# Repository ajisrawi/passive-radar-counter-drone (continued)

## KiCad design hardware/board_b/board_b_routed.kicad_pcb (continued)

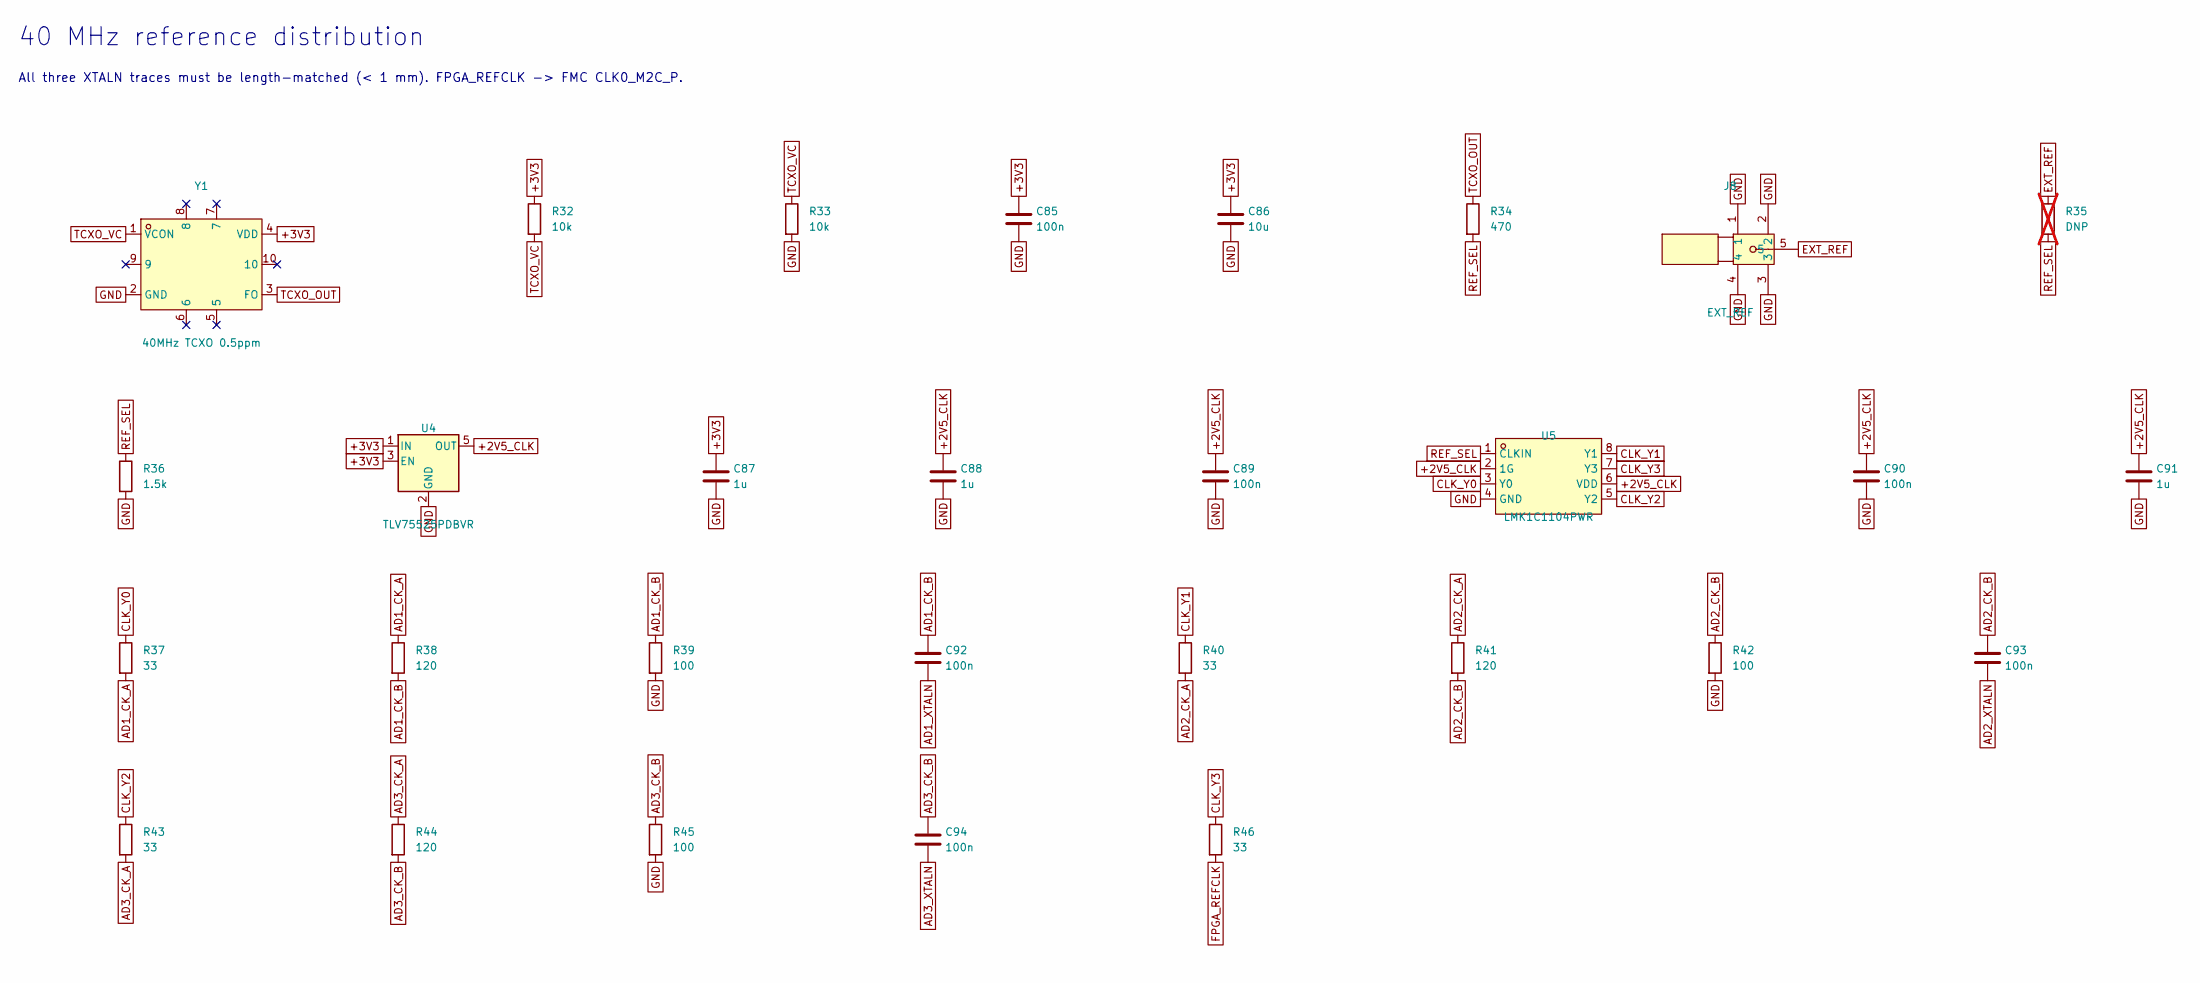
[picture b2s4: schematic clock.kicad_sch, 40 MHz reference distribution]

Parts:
C85, C89, C90, C92, C93, C94: 100n; C_0402_1005Metric; LCSC C1525
C86: 10u; C_0603_1608Metric; LCSC C19702
C87, C88, C91: 1u; C_0402_1005Metric; LCSC C52923
J8: EXT_REF; SMA-TH_BWSMA-KE-Z001; MPN BWSMA-KE-Z001; LCSC C496549
R32, R33: 10k; R_0402_1005Metric; LCSC C25744
R34: 470; R_0402_1005Metric
R35: DNP; R_0402_1005Metric; not fitted
R36: 1.5k; R_0402_1005Metric
R37, R40, R43, R46: 33; R_0402_1005Metric
R38, R41, R44: 120; R_0402_1005Metric
R39, R42, R45: 100; R_0402_1005Metric
U4: TLV75525PDBVR; SOT-23-5
U5: LMK1C1104PWR; TSSOP-8_L4.4-W3.0-P0.65-LS6.4-TL; MPN LMK1C1104PWR; LCSC C1855734
Y1: 40MHz TCXO 0.5ppm; OSC-SMD_10P-L7.0-W5.0-BL; MPN BT0507BH3I507BN40B; LCSC C516506

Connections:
+2V5_CLK: C88.1, C89.1, C90.1, C91.1, U4.5 (OUT), U5.2 (1G), U5.6 (VDD)
+3V3: C85.1, C86.1, C87.1, R32.1, U4.1 (IN), U4.3 (EN), Y1.4 (VDD); also elsewhere on the board
AD1_CK_A: R37.2, R38.1
AD1_CK_B: C92.1, R38.2, R39.1
AD1_XTALN: C92.2; also elsewhere on the board
AD2_CK_A: R40.2, R41.1
AD2_CK_B: C93.1, R41.2, R42.1
AD2_XTALN: C93.2; also elsewhere on the board
AD3_CK_A: R43.2, R44.1
AD3_CK_B: C94.1, R44.2, R45.1
AD3_XTALN: C94.2; also elsewhere on the board
CLK_Y0: R37.1, U5.3 (Y0)
CLK_Y1: R40.1, U5.8 (Y1)
CLK_Y2: R43.1, U5.5 (Y2)
CLK_Y3: R46.1, U5.7 (Y3)
EXT_REF: J8.5, R35.1
FPGA_REFCLK: R46.2; also elsewhere on the board
GND: C85.2, C86.2, C87.2, C88.2, C89.2, C90.2, C91.2, J8.1, J8.2, J8.3, J8.4, R33.2, R36.2, R39.2, R42.2, R45.2, U4.2 (GND), U5.4 (GND), Y1.2 (GND); also elsewhere on the board
REF_SEL: R34.2, R35.2, R36.1, U5.1 (CLKIN)
TCXO_OUT: R34.1, Y1.3 (FO)
TCXO_VC: R32.2, R33.1, Y1.1 (VCON)

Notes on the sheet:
40 MHz reference distribution
All three XTALN traces must be length-matched (< 1 mm). FPGA_REFCLK -> FMC CLK0_M2C_P.

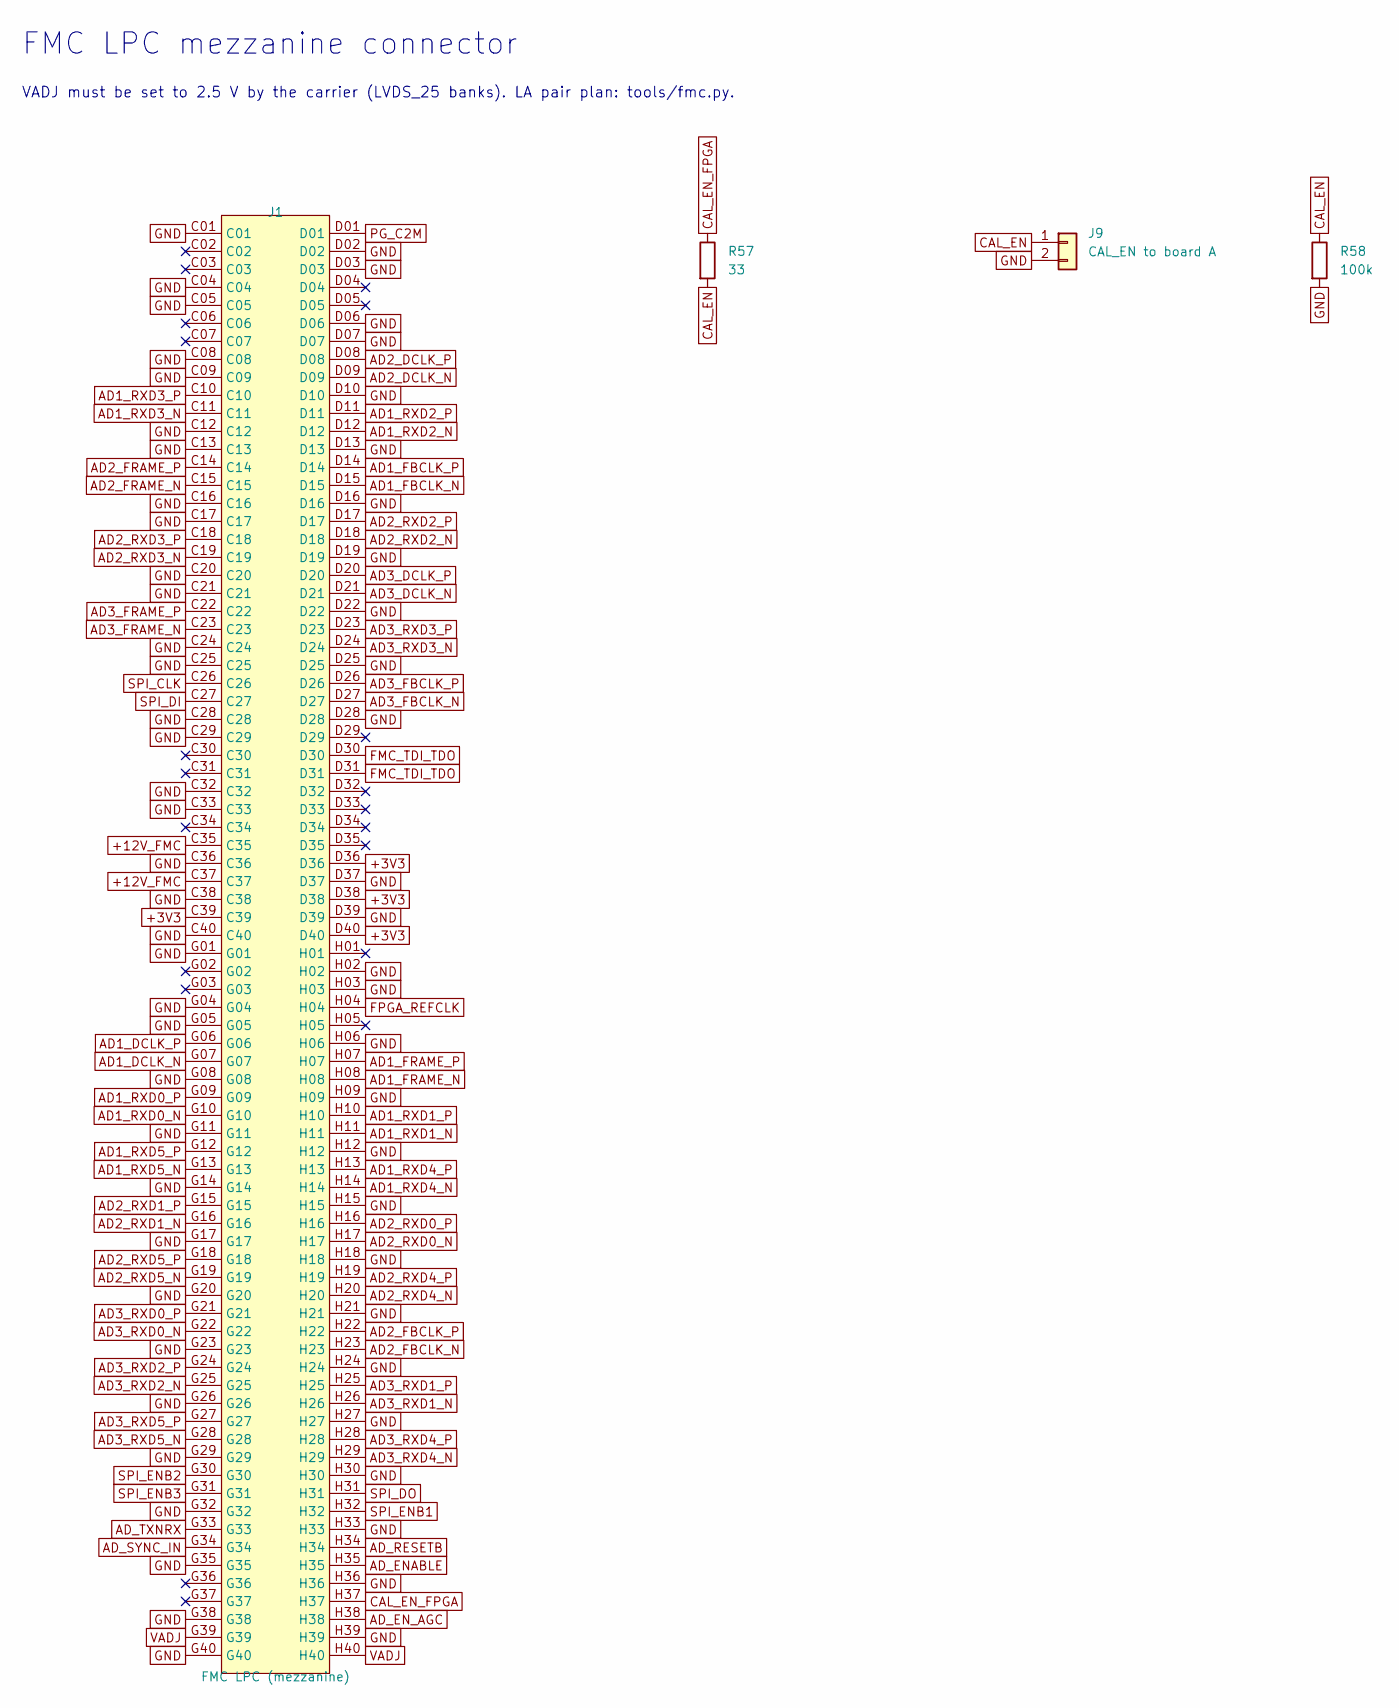
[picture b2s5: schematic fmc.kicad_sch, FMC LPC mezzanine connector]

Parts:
J1: FMC LPC (mezzanine); FPC_SMD_ASP-134604-01; MPN ASP-134604-01; LCSC C2830435
J9: CAL_EN to board A; PinHeader_1x02_P2.54mm_Vertical
R57: 33; R_0402_1005Metric
R58: 100k; R_0402_1005Metric; LCSC C25741

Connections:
+3V3: J1.C39, J1.D36, J1.D38, J1.D40; also elsewhere on the board
+12V_FMC: J1.C35, J1.C37; also elsewhere on the board
AD1_DCLK_N: J1.G07; also elsewhere on the board
AD1_DCLK_P: J1.G06; also elsewhere on the board
AD1_FBCLK_N: J1.D15; also elsewhere on the board
AD1_FBCLK_P: J1.D14; also elsewhere on the board
AD1_FRAME_N: J1.H08; also elsewhere on the board
AD1_FRAME_P: J1.H07; also elsewhere on the board
AD1_RXD0_N: J1.G10; also elsewhere on the board
AD1_RXD0_P: J1.G09; also elsewhere on the board
AD1_RXD1_N: J1.H11; also elsewhere on the board
AD1_RXD1_P: J1.H10; also elsewhere on the board
AD1_RXD2_N: J1.D12; also elsewhere on the board
AD1_RXD2_P: J1.D11; also elsewhere on the board
AD1_RXD3_N: J1.C11; also elsewhere on the board
AD1_RXD3_P: J1.C10; also elsewhere on the board
AD1_RXD4_N: J1.H14; also elsewhere on the board
AD1_RXD4_P: J1.H13; also elsewhere on the board
AD1_RXD5_N: J1.G13; also elsewhere on the board
AD1_RXD5_P: J1.G12; also elsewhere on the board
AD2_DCLK_N: J1.D09; also elsewhere on the board
AD2_DCLK_P: J1.D08; also elsewhere on the board
AD2_FBCLK_N: J1.H23; also elsewhere on the board
AD2_FBCLK_P: J1.H22; also elsewhere on the board
AD2_FRAME_N: J1.C15; also elsewhere on the board
AD2_FRAME_P: J1.C14; also elsewhere on the board
AD2_RXD0_N: J1.H17; also elsewhere on the board
AD2_RXD0_P: J1.H16; also elsewhere on the board
AD2_RXD1_N: J1.G16; also elsewhere on the board
AD2_RXD1_P: J1.G15; also elsewhere on the board
AD2_RXD2_N: J1.D18; also elsewhere on the board
AD2_RXD2_P: J1.D17; also elsewhere on the board
AD2_RXD3_N: J1.C19; also elsewhere on the board
AD2_RXD3_P: J1.C18; also elsewhere on the board
AD2_RXD4_N: J1.H20; also elsewhere on the board
AD2_RXD4_P: J1.H19; also elsewhere on the board
AD2_RXD5_N: J1.G19; also elsewhere on the board
AD2_RXD5_P: J1.G18; also elsewhere on the board
AD3_DCLK_N: J1.D21; also elsewhere on the board
AD3_DCLK_P: J1.D20; also elsewhere on the board
AD3_FBCLK_N: J1.D27; also elsewhere on the board
AD3_FBCLK_P: J1.D26; also elsewhere on the board
AD3_FRAME_N: J1.C23; also elsewhere on the board
AD3_FRAME_P: J1.C22; also elsewhere on the board
AD3_RXD0_N: J1.G22; also elsewhere on the board
AD3_RXD0_P: J1.G21; also elsewhere on the board
AD3_RXD1_N: J1.H26; also elsewhere on the board
AD3_RXD1_P: J1.H25; also elsewhere on the board
AD3_RXD2_N: J1.G25; also elsewhere on the board
AD3_RXD2_P: J1.G24; also elsewhere on the board
AD3_RXD3_N: J1.D24; also elsewhere on the board
AD3_RXD3_P: J1.D23; also elsewhere on the board
AD3_RXD4_N: J1.H29; also elsewhere on the board
AD3_RXD4_P: J1.H28; also elsewhere on the board
AD3_RXD5_N: J1.G28; also elsewhere on the board
AD3_RXD5_P: J1.G27; also elsewhere on the board
AD_ENABLE: J1.H35; also elsewhere on the board
AD_EN_AGC: J1.H38; also elsewhere on the board
AD_RESETB: J1.H34; also elsewhere on the board
AD_SYNC_IN: J1.G34; also elsewhere on the board
AD_TXNRX: J1.G33; also elsewhere on the board
CAL_EN: J9.1, R57.2, R58.1
CAL_EN_FPGA: J1.H37, R57.1
FMC_TDI_TDO: J1.D30, J1.D31
FPGA_REFCLK: J1.H04; also elsewhere on the board
GND: J1.C01, J1.C04, J1.C05, J1.C08, J1.C09, J1.C12, J1.C13, J1.C16, J1.C17, J1.C20, J1.C21, J1.C24, J1.C25, J1.C28, J1.C29, J1.C32, J1.C33, J1.C36, J1.C38, J1.C40, J1.D02, J1.D03, J1.D06, J1.D07, J1.D10, J1.D13, J1.D16, J1.D19, J1.D22, J1.D25, J1.D28, J1.D37, J1.D39, J1.G01, J1.G04, J1.G05, J1.G08, J1.G11, J1.G14, J1.G17, J1.G20, J1.G23, J1.G26, J1.G29, J1.G32, J1.G35, J1.G38, J1.G40, J1.H02, J1.H03, J1.H06, J1.H09, J1.H12, J1.H15, J1.H18, J1.H21, J1.H24, J1.H27, J1.H30, J1.H33, J1.H36, J1.H39, J9.2, R58.2; also elsewhere on the board
PG_C2M: J1.D01; also elsewhere on the board
SPI_CLK: J1.C26; also elsewhere on the board
SPI_DI: J1.C27; also elsewhere on the board
SPI_DO: J1.H31; also elsewhere on the board
SPI_ENB1: J1.H32; also elsewhere on the board
SPI_ENB2: J1.G30; also elsewhere on the board
SPI_ENB3: J1.G31; also elsewhere on the board
VADJ: J1.G39, J1.H40; also elsewhere on the board

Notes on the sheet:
FMC LPC mezzanine connector
VADJ must be set to 2.5 V by the carrier (LVDS_25 banks). LA pair plan: tools/fmc.py.

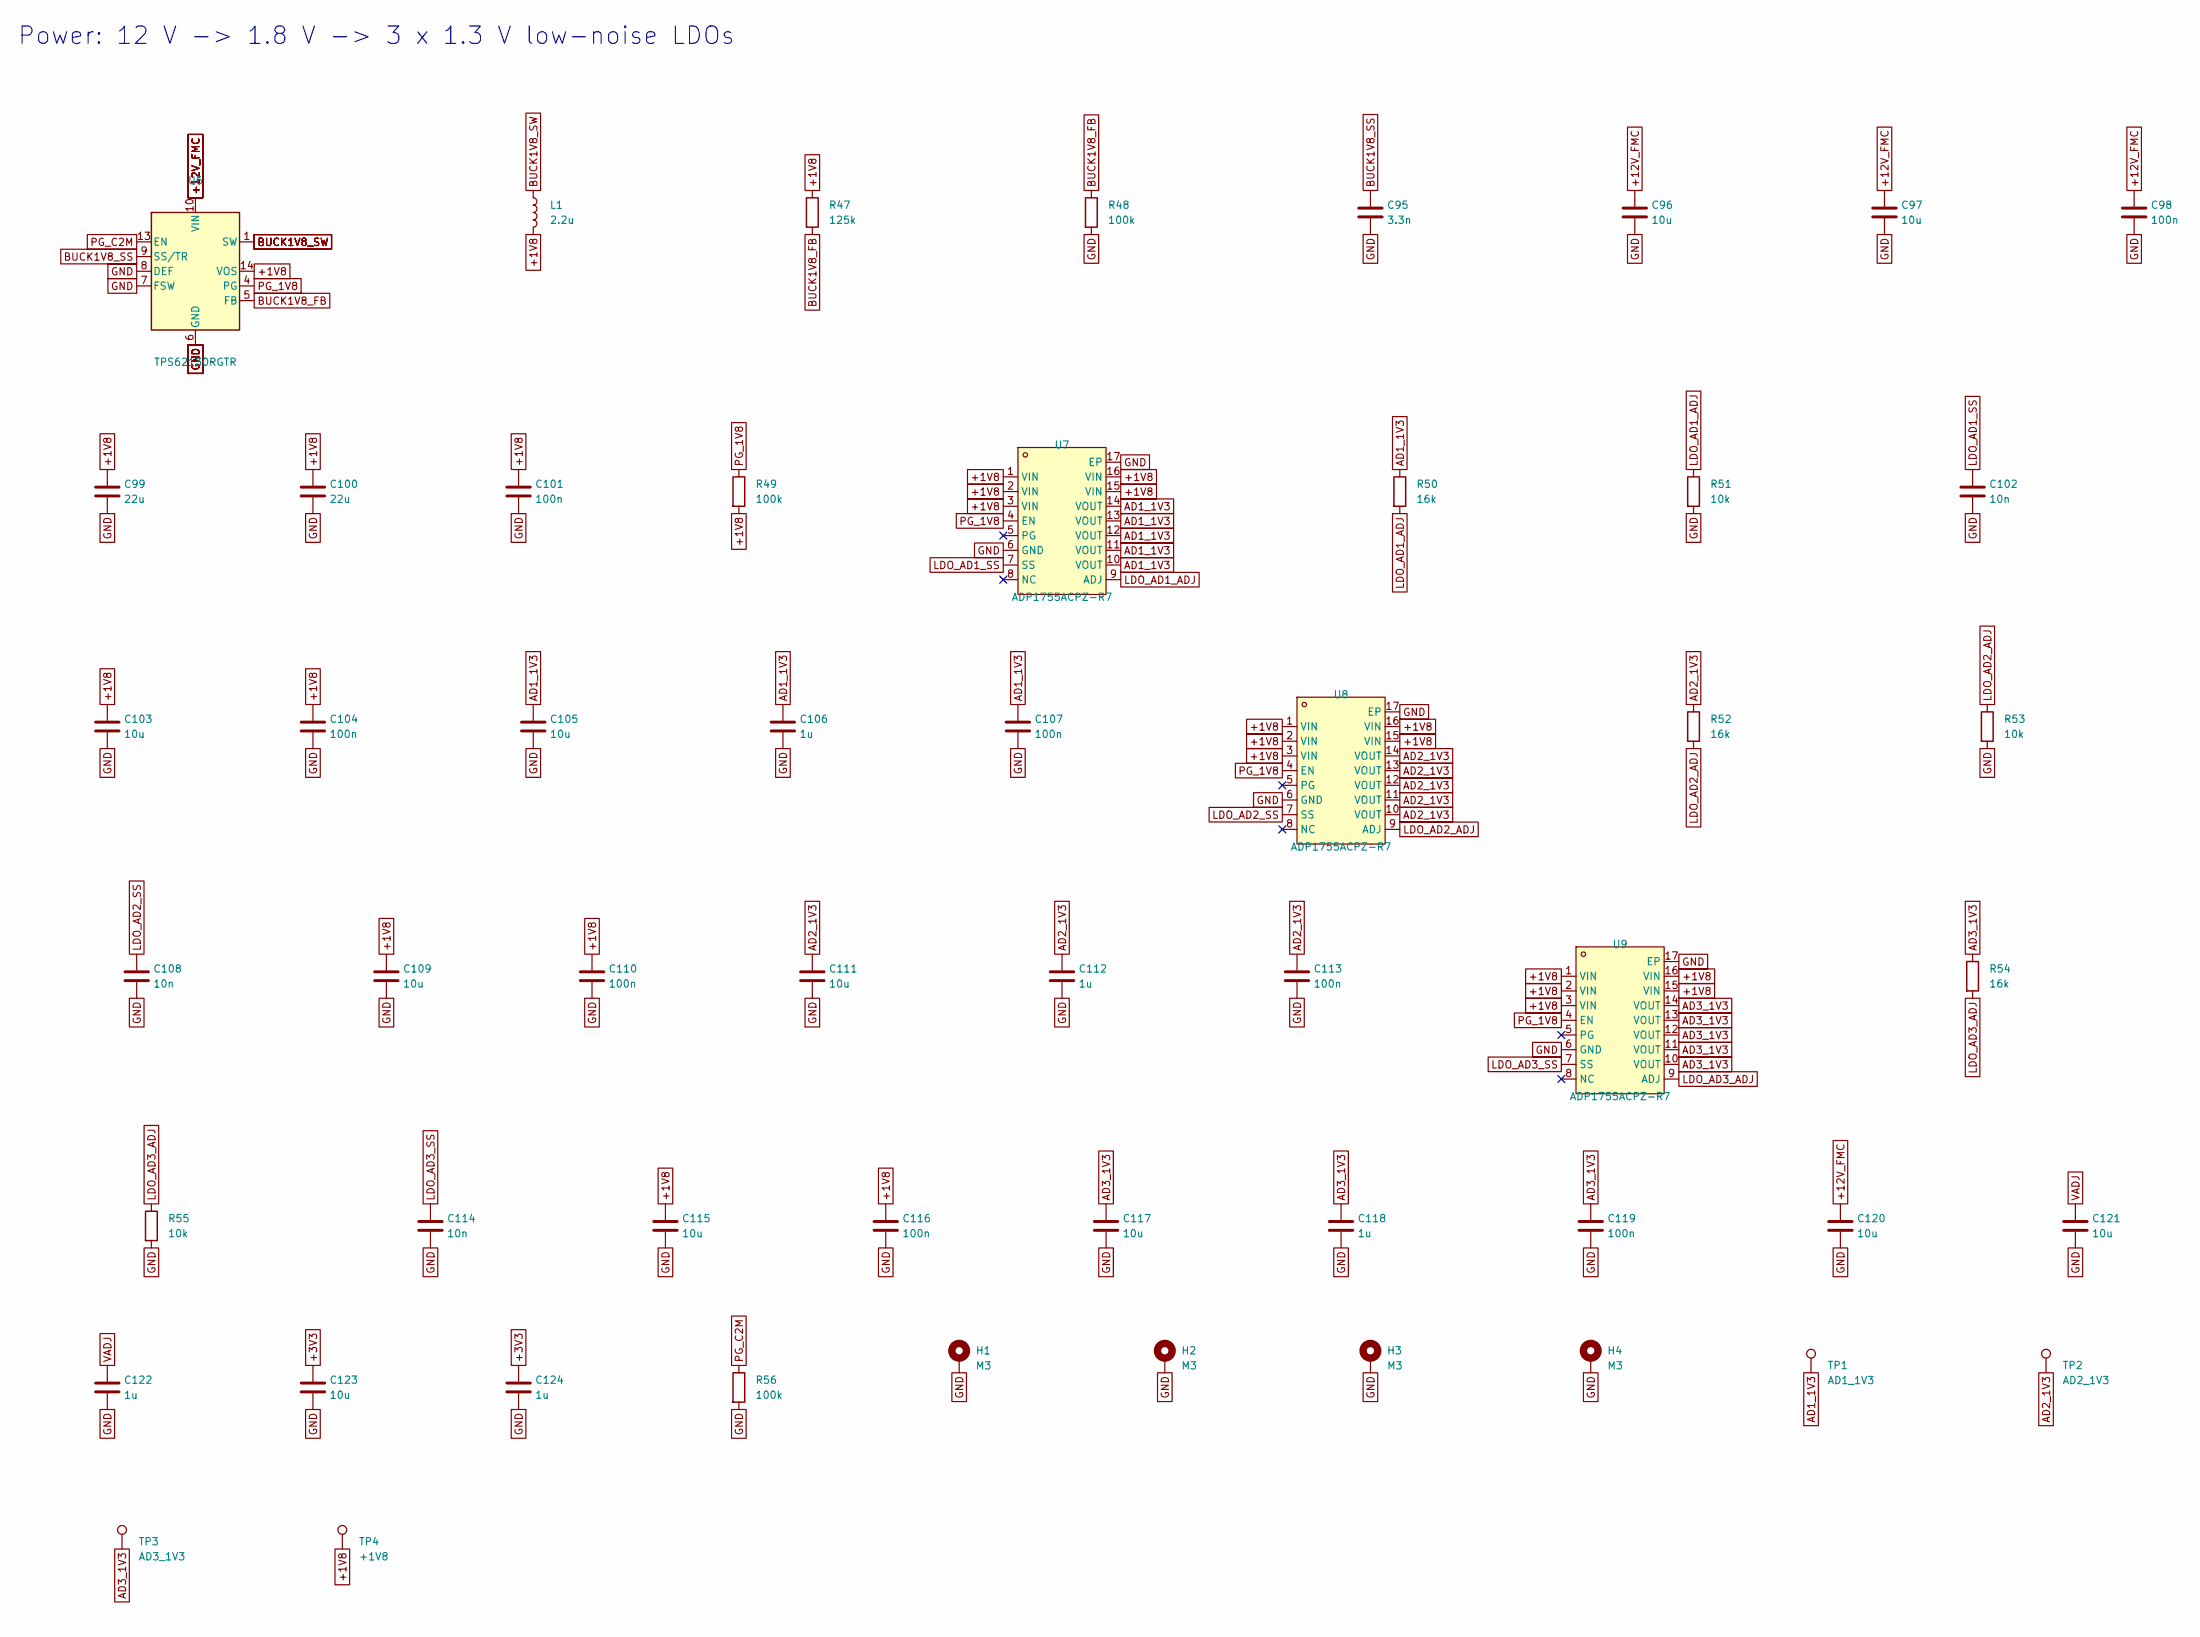
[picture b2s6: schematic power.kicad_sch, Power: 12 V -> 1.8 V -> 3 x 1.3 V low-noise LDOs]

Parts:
C95: 3.3n; C_0402_1005Metric
C96, C97, C120: 10u; C_0805_2012Metric
C98, C101, C104, C107, C110, C113, C116, C119: 100n; C_0402_1005Metric; LCSC C1525
C99, C100: 22u; C_0805_2012Metric; LCSC C45783
C102, C108, C114: 10n; C_0402_1005Metric; LCSC C15195
C103, C105, C109, C111, C115, C117, C121, C123: 10u; C_0603_1608Metric; LCSC C19702
C106, C112, C118, C122, C124: 1u; C_0402_1005Metric; LCSC C52923
H1, H2, H3, H4: M3; MountingHole_3.2mm_M3_Pad_Via
L1: 2.2u; L_Bourns-SRN4018; MPN SRN4018-2R2M
R47: 125k; R_0402_1005Metric
R48, R49, R56: 100k; R_0402_1005Metric; LCSC C25741
R50, R52, R54: 16k; R_0402_1005Metric; Tolerance 1%
R51, R53, R55: 10k; R_0402_1005Metric; Tolerance 1%; LCSC C25744
TP1: AD1_1V3; TestPoint_Pad_D1.0mm
TP2: AD2_1V3; TestPoint_Pad_D1.0mm
TP3: AD3_1V3; TestPoint_Pad_D1.0mm
TP4: +1V8; TestPoint_Pad_D1.0mm
U6: TPS62130RGTR; VQFN-16-1EP_3x3mm_P0.5mm_EP1.68x1.68mm; MPN TPS62130RGTR; LCSC C43590
U7, U8, U9: ADP1755ACPZ-R7; LFCSP-16_L4.0-W4.0-P0.65-BL-EP2.2; MPN ADP1755ACPZ-R7; LCSC C403695

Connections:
+1V8: C99.1, C100.1, C101.1, C103.1, C104.1, C109.1, C110.1, C115.1, C116.1, L1.2, R47.1, R49.2, TP4.1, U6.14 (VOS), U7.1 (VIN), U7.2 (VIN), U7.3 (VIN), U7.15 (VIN), U7.16 (VIN), U8.1 (VIN), U8.2 (VIN), U8.3 (VIN), U8.15 (VIN), U8.16 (VIN), U9.1 (VIN), U9.2 (VIN), U9.3 (VIN), U9.15 (VIN), U9.16 (VIN)
+3V3: C123.1, C124.1; also elsewhere on the board
+12V_FMC: C96.1, C97.1, C98.1, C120.1, U6.10 (VIN), U6.11 (VIN), U6.12 (VIN); also elsewhere on the board
AD1_1V3: C105.1, C106.1, C107.1, R50.1, TP1.1, U7.10 (VOUT), U7.11 (VOUT), U7.12 (VOUT), U7.13 (VOUT), U7.14 (VOUT); also elsewhere on the board
AD2_1V3: C111.1, C112.1, C113.1, R52.1, TP2.1, U8.10 (VOUT), U8.11 (VOUT), U8.12 (VOUT), U8.13 (VOUT), U8.14 (VOUT); also elsewhere on the board
AD3_1V3: C117.1, C118.1, C119.1, R54.1, TP3.1, U9.10 (VOUT), U9.11 (VOUT), U9.12 (VOUT), U9.13 (VOUT), U9.14 (VOUT); also elsewhere on the board
BUCK1V8_FB: R47.2, R48.1, U6.5 (FB)
BUCK1V8_SS: C95.1, U6.9 (SS/TR)
BUCK1V8_SW: L1.1, U6.1 (SW), U6.2 (SW), U6.3 (SW)
GND: C95.2, C96.2, C97.2, C98.2, C99.2, C100.2, C101.2, C102.2, C103.2, C104.2, C105.2, C106.2, C107.2, C108.2, C109.2, C110.2, C111.2, C112.2, C113.2, C114.2, C115.2, C116.2, C117.2, C118.2, C119.2, C120.2, C121.2, C122.2, C123.2, C124.2, H1.1, H2.1, H3.1, H4.1, R48.2, R51.2, R53.2, R55.2, R56.2, U6.6 (GND), U6.7 (FSW), U6.8 (DEF), U6.15 (GND), U6.16 (GND), U6.17 (GND), U7.6 (GND), U7.17 (EP), U8.6 (GND), U8.17 (EP), U9.6 (GND), U9.17 (EP); also elsewhere on the board
LDO_AD1_ADJ: R50.2, R51.1, U7.9 (ADJ)
LDO_AD1_SS: C102.1, U7.7 (SS)
LDO_AD2_ADJ: R52.2, R53.1, U8.9 (ADJ)
LDO_AD2_SS: C108.1, U8.7 (SS)
LDO_AD3_ADJ: R54.2, R55.1, U9.9 (ADJ)
LDO_AD3_SS: C114.1, U9.7 (SS)
PG_1V8: R49.1, U6.4 (PG), U7.4 (EN), U8.4 (EN), U9.4 (EN)
PG_C2M: R56.1, U6.13 (EN); also elsewhere on the board
VADJ: C121.1, C122.1; also elsewhere on the board

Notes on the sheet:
Power: 12 V -> 1.8 V -> 3 x 1.3 V low-noise LDOs

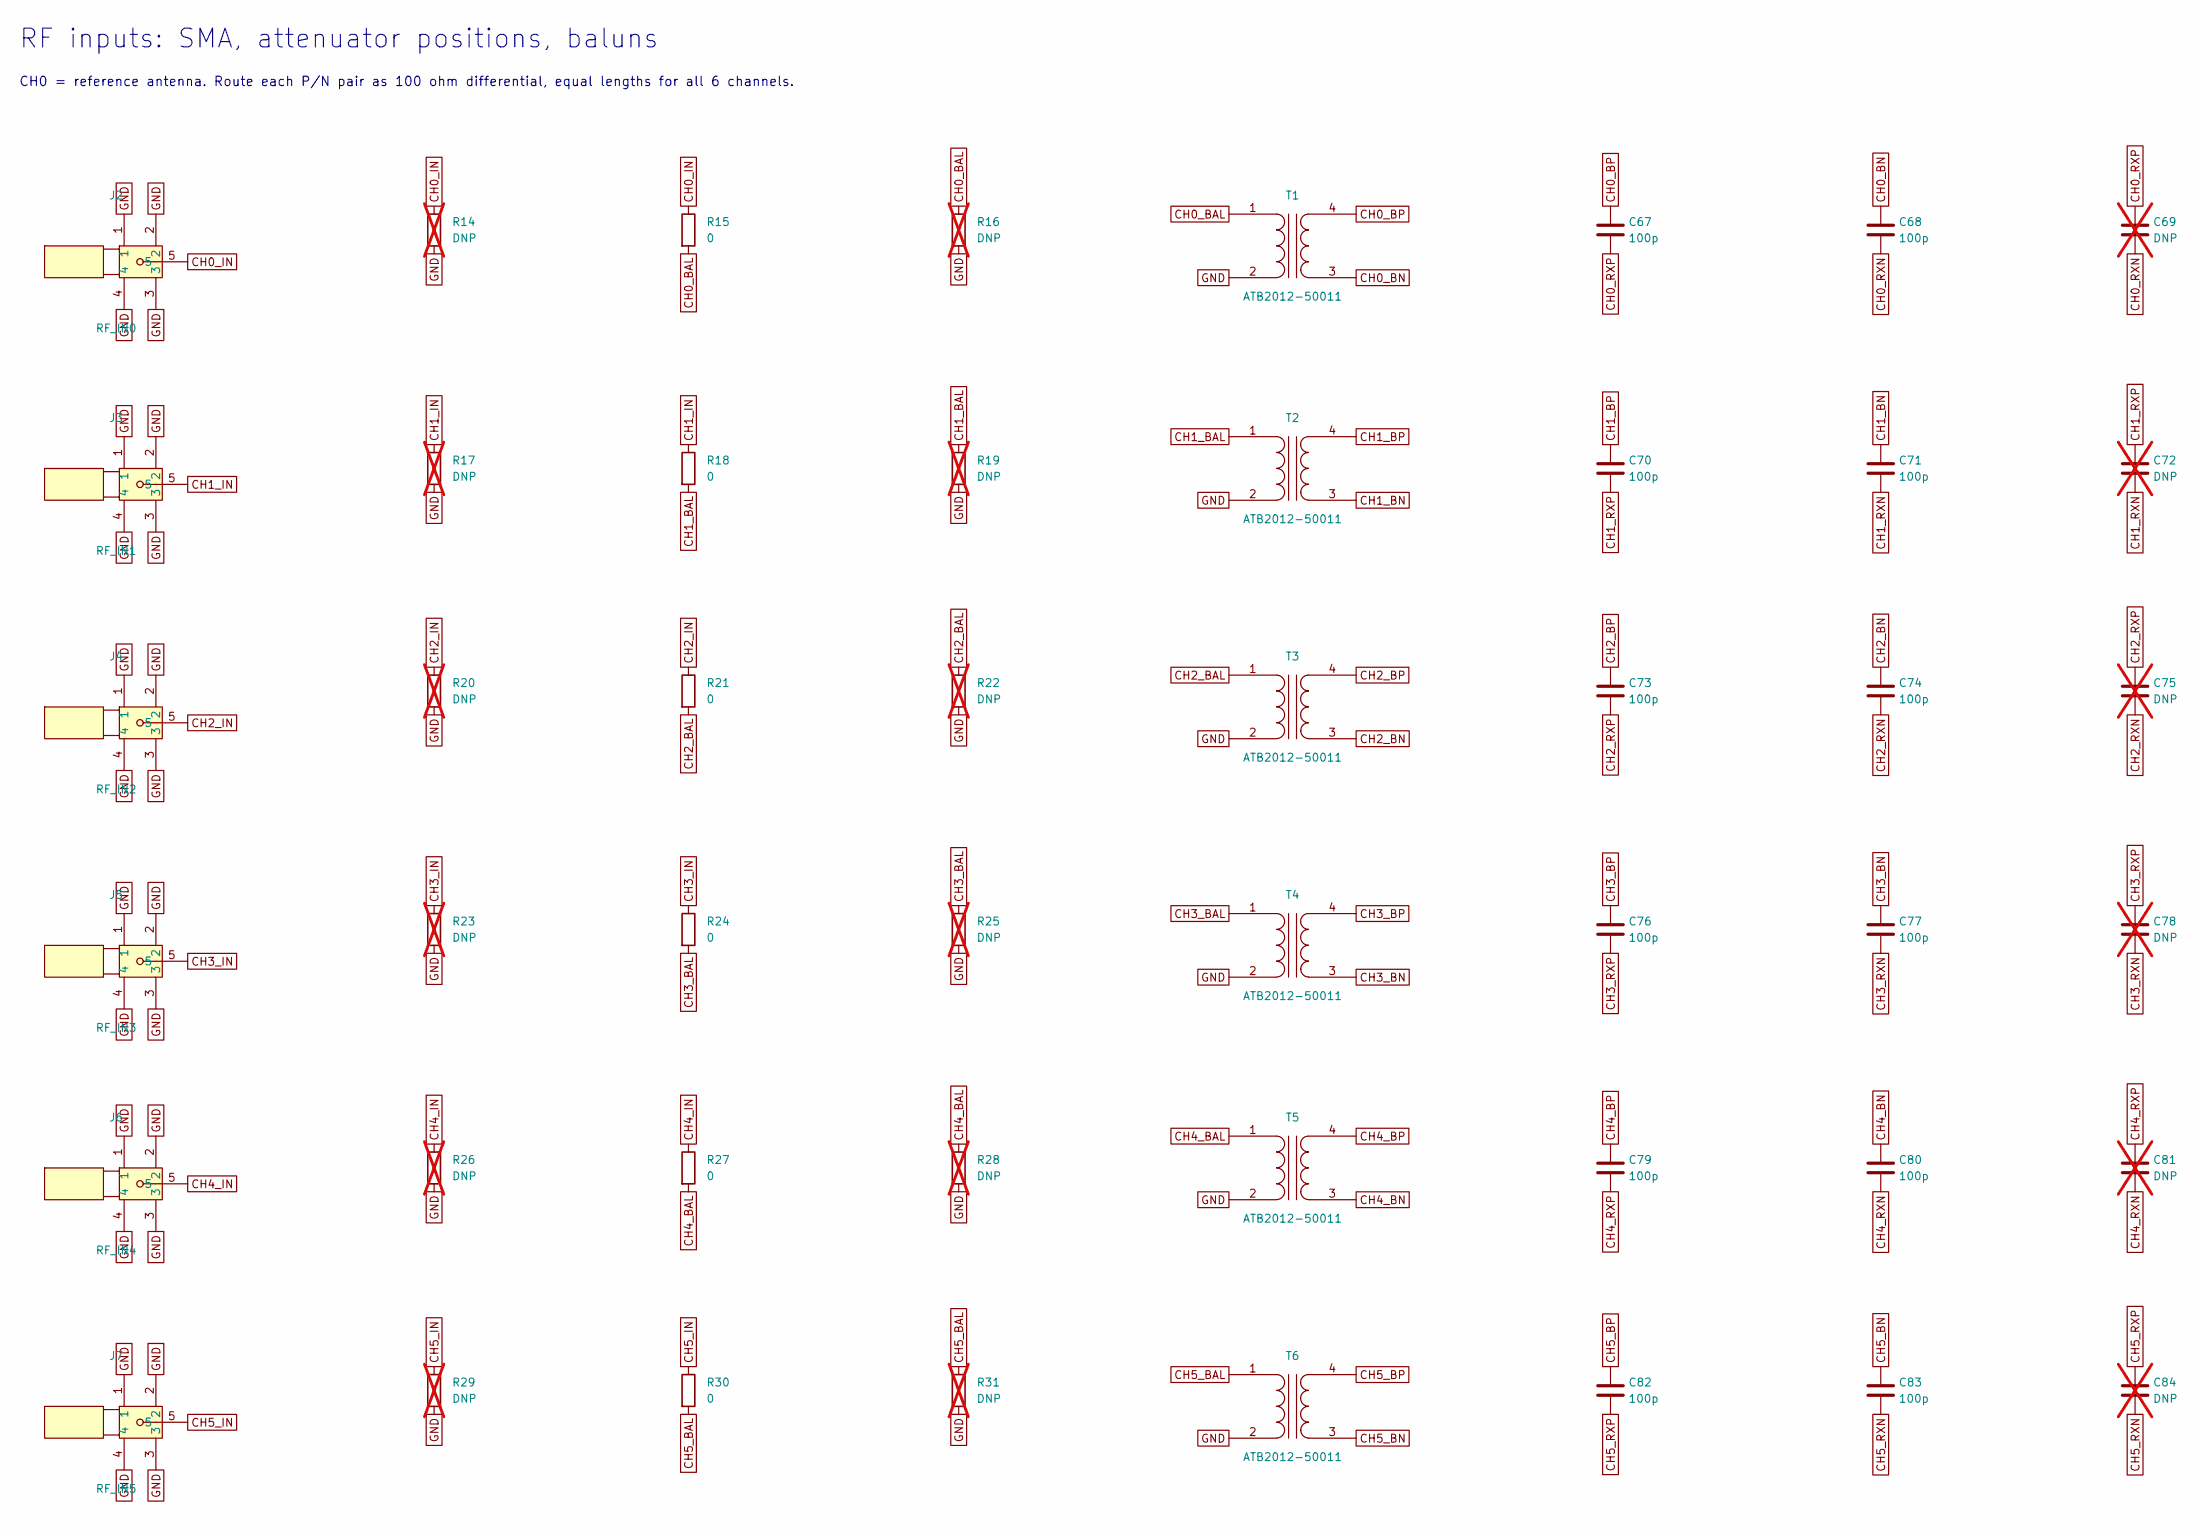
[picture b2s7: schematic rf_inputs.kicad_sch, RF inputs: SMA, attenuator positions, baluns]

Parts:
C67, C68, C70, C71, C73, C74, C76, C77, C79, C80, C82, C83: 100p; C_0402_1005Metric
C69, C72, C75, C78, C81, C84: DNP; C_0402_1005Metric; not fitted
J2: RF_IN0; SMA-TH_BWSMA-KE-Z001; MPN BWSMA-KE-Z001; LCSC C496549
J3: RF_IN1; SMA-TH_BWSMA-KE-Z001; MPN BWSMA-KE-Z001; LCSC C496549
J4: RF_IN2; SMA-TH_BWSMA-KE-Z001; MPN BWSMA-KE-Z001; LCSC C496549
J5: RF_IN3; SMA-TH_BWSMA-KE-Z001; MPN BWSMA-KE-Z001; LCSC C496549
J6: RF_IN4; SMA-TH_BWSMA-KE-Z001; MPN BWSMA-KE-Z001; LCSC C496549
J7: RF_IN5; SMA-TH_BWSMA-KE-Z001; MPN BWSMA-KE-Z001; LCSC C496549
R14, R16, R17, R19, R20, R22, R23, R25, R26, R28, R29, R31: DNP; R_0402_1005Metric; not fitted
R15, R18, R21, R24, R27, R30: 0; R_0402_1005Metric; LCSC C17168
T1, T2, T3, T4, T5, T6: ATB2012-50011; XFMR-SMD_ATB2012-50011-T000; MPN ATB2012-50011-T000; LCSC C92015

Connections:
CH0_BAL: R15.2, R16.1, T1.1 (AA)
CH0_BN: C68.1, T1.3 (SA)
CH0_BP: C67.1, T1.4 (SB)
CH0_IN: J2.5, R14.1, R15.1
CH0_RXN: C68.2, C69.2; also elsewhere on the board
CH0_RXP: C67.2, C69.1; also elsewhere on the board
CH1_BAL: R18.2, R19.1, T2.1 (AA)
CH1_BN: C71.1, T2.3 (SA)
CH1_BP: C70.1, T2.4 (SB)
CH1_IN: J3.5, R17.1, R18.1
CH1_RXN: C71.2, C72.2; also elsewhere on the board
CH1_RXP: C70.2, C72.1; also elsewhere on the board
CH2_BAL: R21.2, R22.1, T3.1 (AA)
CH2_BN: C74.1, T3.3 (SA)
CH2_BP: C73.1, T3.4 (SB)
CH2_IN: J4.5, R20.1, R21.1
CH2_RXN: C74.2, C75.2; also elsewhere on the board
CH2_RXP: C73.2, C75.1; also elsewhere on the board
CH3_BAL: R24.2, R25.1, T4.1 (AA)
CH3_BN: C77.1, T4.3 (SA)
CH3_BP: C76.1, T4.4 (SB)
CH3_IN: J5.5, R23.1, R24.1
CH3_RXN: C77.2, C78.2; also elsewhere on the board
CH3_RXP: C76.2, C78.1; also elsewhere on the board
CH4_BAL: R27.2, R28.1, T5.1 (AA)
CH4_BN: C80.1, T5.3 (SA)
CH4_BP: C79.1, T5.4 (SB)
CH4_IN: J6.5, R26.1, R27.1
CH4_RXN: C80.2, C81.2; also elsewhere on the board
CH4_RXP: C79.2, C81.1; also elsewhere on the board
CH5_BAL: R30.2, R31.1, T6.1 (AA)
CH5_BN: C83.1, T6.3 (SA)
CH5_BP: C82.1, T6.4 (SB)
CH5_IN: J7.5, R29.1, R30.1
CH5_RXN: C83.2, C84.2; also elsewhere on the board
CH5_RXP: C82.2, C84.1; also elsewhere on the board
GND: J2.1, J2.2, J2.3, J2.4, J3.1, J3.2, J3.3, J3.4, J4.1, J4.2, J4.3, J4.4, J5.1, J5.2, J5.3, J5.4, J6.1, J6.2, J6.3, J6.4, J7.1, J7.2, J7.3, J7.4, R14.2, R16.2, R17.2, R19.2, R20.2, R22.2, R23.2, R25.2, R26.2, R28.2, R29.2, R31.2, T1.2 (AB), T2.2 (AB), T3.2 (AB), T4.2 (AB), T5.2 (AB), T6.2 (AB); also elsewhere on the board

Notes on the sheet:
RF inputs: SMA, attenuator positions, baluns
CH0 = reference antenna. Route each P/N pair as 100 ohm differential, equal lengths for all 6 channels.

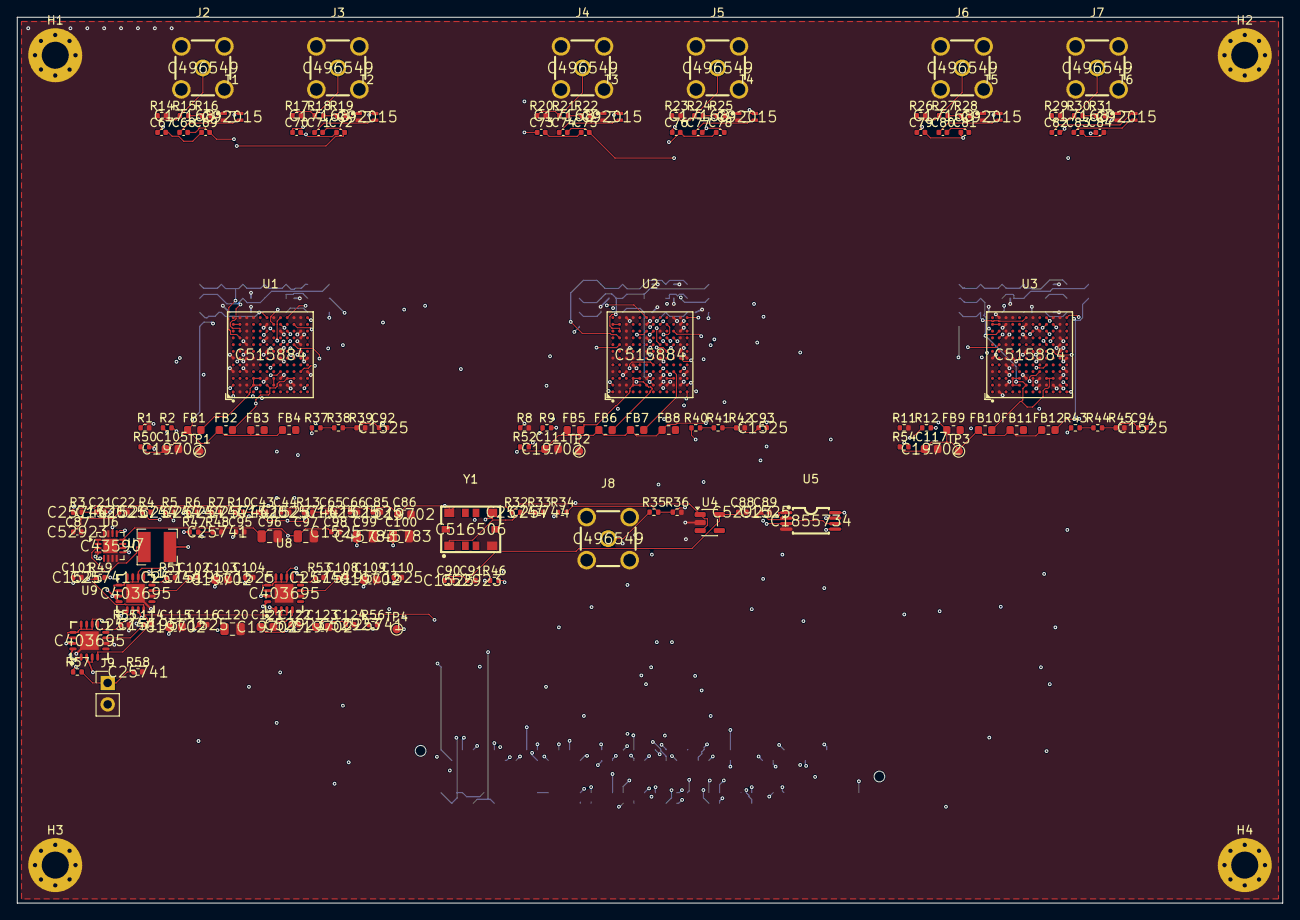
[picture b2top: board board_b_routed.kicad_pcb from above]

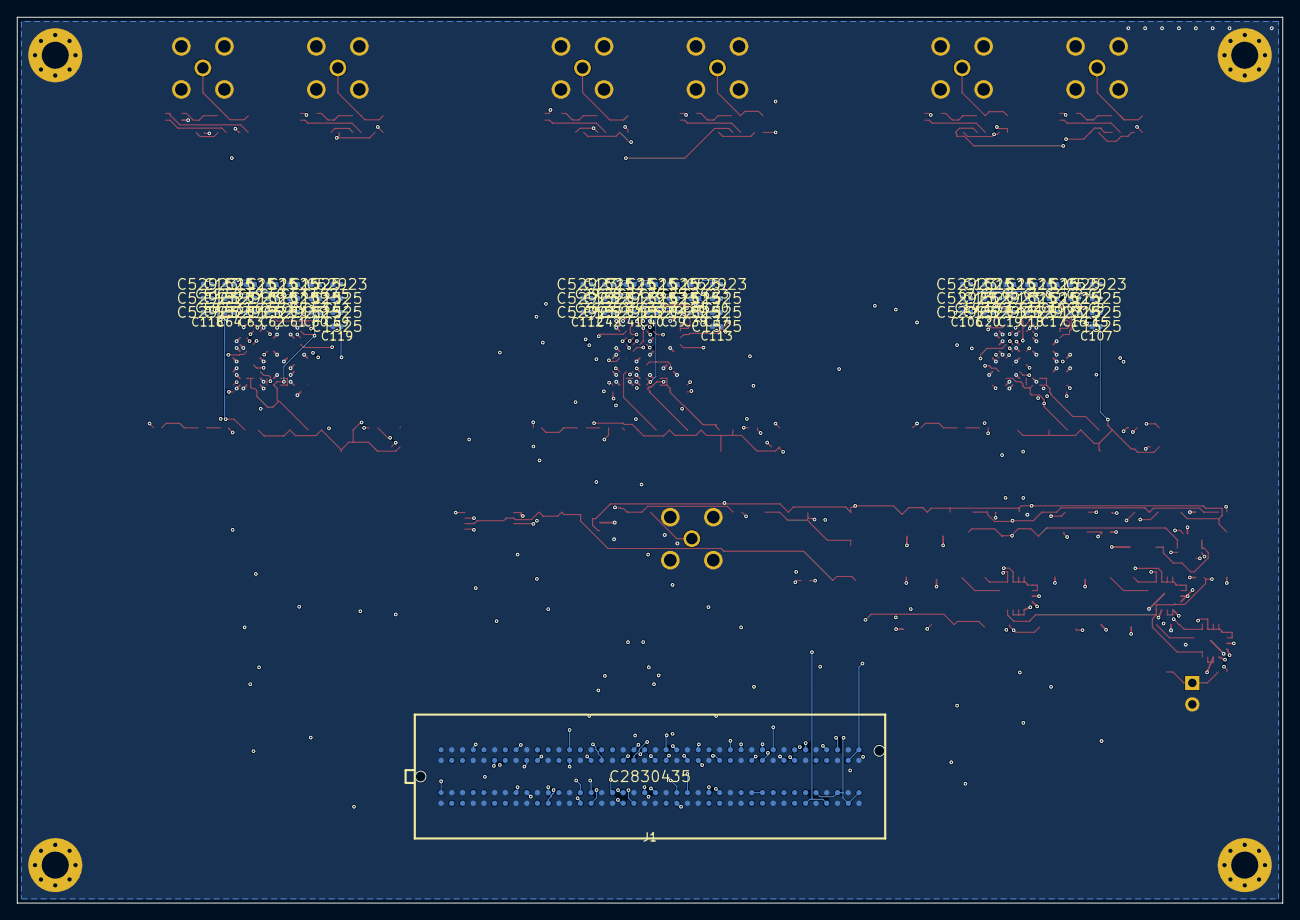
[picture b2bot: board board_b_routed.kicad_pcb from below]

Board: 8 copper layers, 150.0 x 105.0 mm, 228 parts (67 on the bottom side), 166 nets.

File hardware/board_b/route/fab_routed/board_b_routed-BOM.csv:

Comment,Designator,Footprint,JLCPCB Part #
1u,"C1,C7,C12,C14,C17,C19,C23,C29,C34,C36,C39,C41,C45,C51,C56,C58,C61,C63,C106,C112,C118",1,
100n,"C2,C3,C4,C5,C6,C8,C9,C10,C11,C13,C15,C16,C18,C20,C24,C25,C26,C27,C28,C30,C31,C32,C33,C35,C37,C38,C40,C42,C46,C47,C48,C49,C50,C52,C53,C54,C55,C57,C59,C60,C62,C64,C107,C113,C119",1,
100n,"C21,C22,C43,C44,C65,C66,C85,C89,C90,C92,C93,C94,C98,C101,C104,C110,C116",C_0402_1005Metric,
100p,"C67,C68,C70,C71,C73,C74,C76,C77,C79,C80,C82,C83",C_0402_1005Metric,
10u,"C86,C103,C105,C109,C111,C115,C117,C121,C123",C_0603_1608Metric,
1u,"C87,C88,C91,C122,C124",C_0402_1005Metric,
3.3n,C95,C_0402_1005Metric,
10u,"C96,C97,C120",C_0805_2012Metric,
22u,"C99,C100",C_0805_2012Metric,
10n,"C102,C108,C114",C_0402_1005Metric,
600R@100MHz,"FB1,FB2,FB3,FB4,FB5,FB6,FB7,FB8,FB9,FB10,FB11,FB12",L_0603_1608Metric,
FMC LPC (mezzanine),J1,FPC_SMD_ASP-134604-01,
RF_IN0,J2,SMA-TH_BWSMA-KE-Z001,
RF_IN1,J3,SMA-TH_BWSMA-KE-Z001,
RF_IN2,J4,SMA-TH_BWSMA-KE-Z001,
RF_IN3,J5,SMA-TH_BWSMA-KE-Z001,
RF_IN4,J6,SMA-TH_BWSMA-KE-Z001,
RF_IN5,J7,SMA-TH_BWSMA-KE-Z001,
EXT_REF,J8,SMA-TH_BWSMA-KE-Z001,
CAL_EN to board A,J9,PinHeader_1x02_P2.54mm_Vertical,
2.2u,L1,L_Bourns-SRN4018,
14.3k,"R1,R8,R11",R_0402_1005Metric,
22,"R2,R9,R12",R_0402_1005Metric,
10k,"R3,R4,R5,R6,R7,R10,R13,R32,R33,R51,R53,R55",R_0402_1005Metric,
0,"R15,R18,R21,R24,R27,R30",R_0402_1005Metric,
470,R34,R_0402_1005Metric,
1.5k,R36,R_0402_1005Metric,
33,"R37,R40,R43,R46,R57",R_0402_1005Metric,
120,"R38,R41,R44",R_0402_1005Metric,
100,"R39,R42,R45",R_0402_1005Metric,
125k,R47,R_0402_1005Metric,
100k,"R48,R49,R56,R58",R_0402_1005Metric,
16k,"R50,R52,R54",R_0402_1005Metric,
ATB2012-50011,"T1,T2,T3,T4,T5,T6",XFMR-SMD_ATB2012-50011-T000,
AD9361BBCZ,"U1,U2,U3",CSPBGA-144_L10.0-W10.0-R12-C12-P0.80-BL,
TLV75525PDBVR,U4,SOT-23-5,
LMK1C1104PWR,U5,TSSOP-8_L4.4-W3.0-P0.65-LS6.4-TL,
TPS62130RGTR,U6,VQFN-16-1EP_3x3mm_P0.5mm_EP1.68x1.68mm,
ADP1755ACPZ-R7,"U7,U8,U9",LFCSP-16_L4.0-W4.0-P0.65-BL-EP2.2,
40MHz TCXO 0.5ppm,Y1,OSC-SMD_10P-L7.0-W5.0-BL,
